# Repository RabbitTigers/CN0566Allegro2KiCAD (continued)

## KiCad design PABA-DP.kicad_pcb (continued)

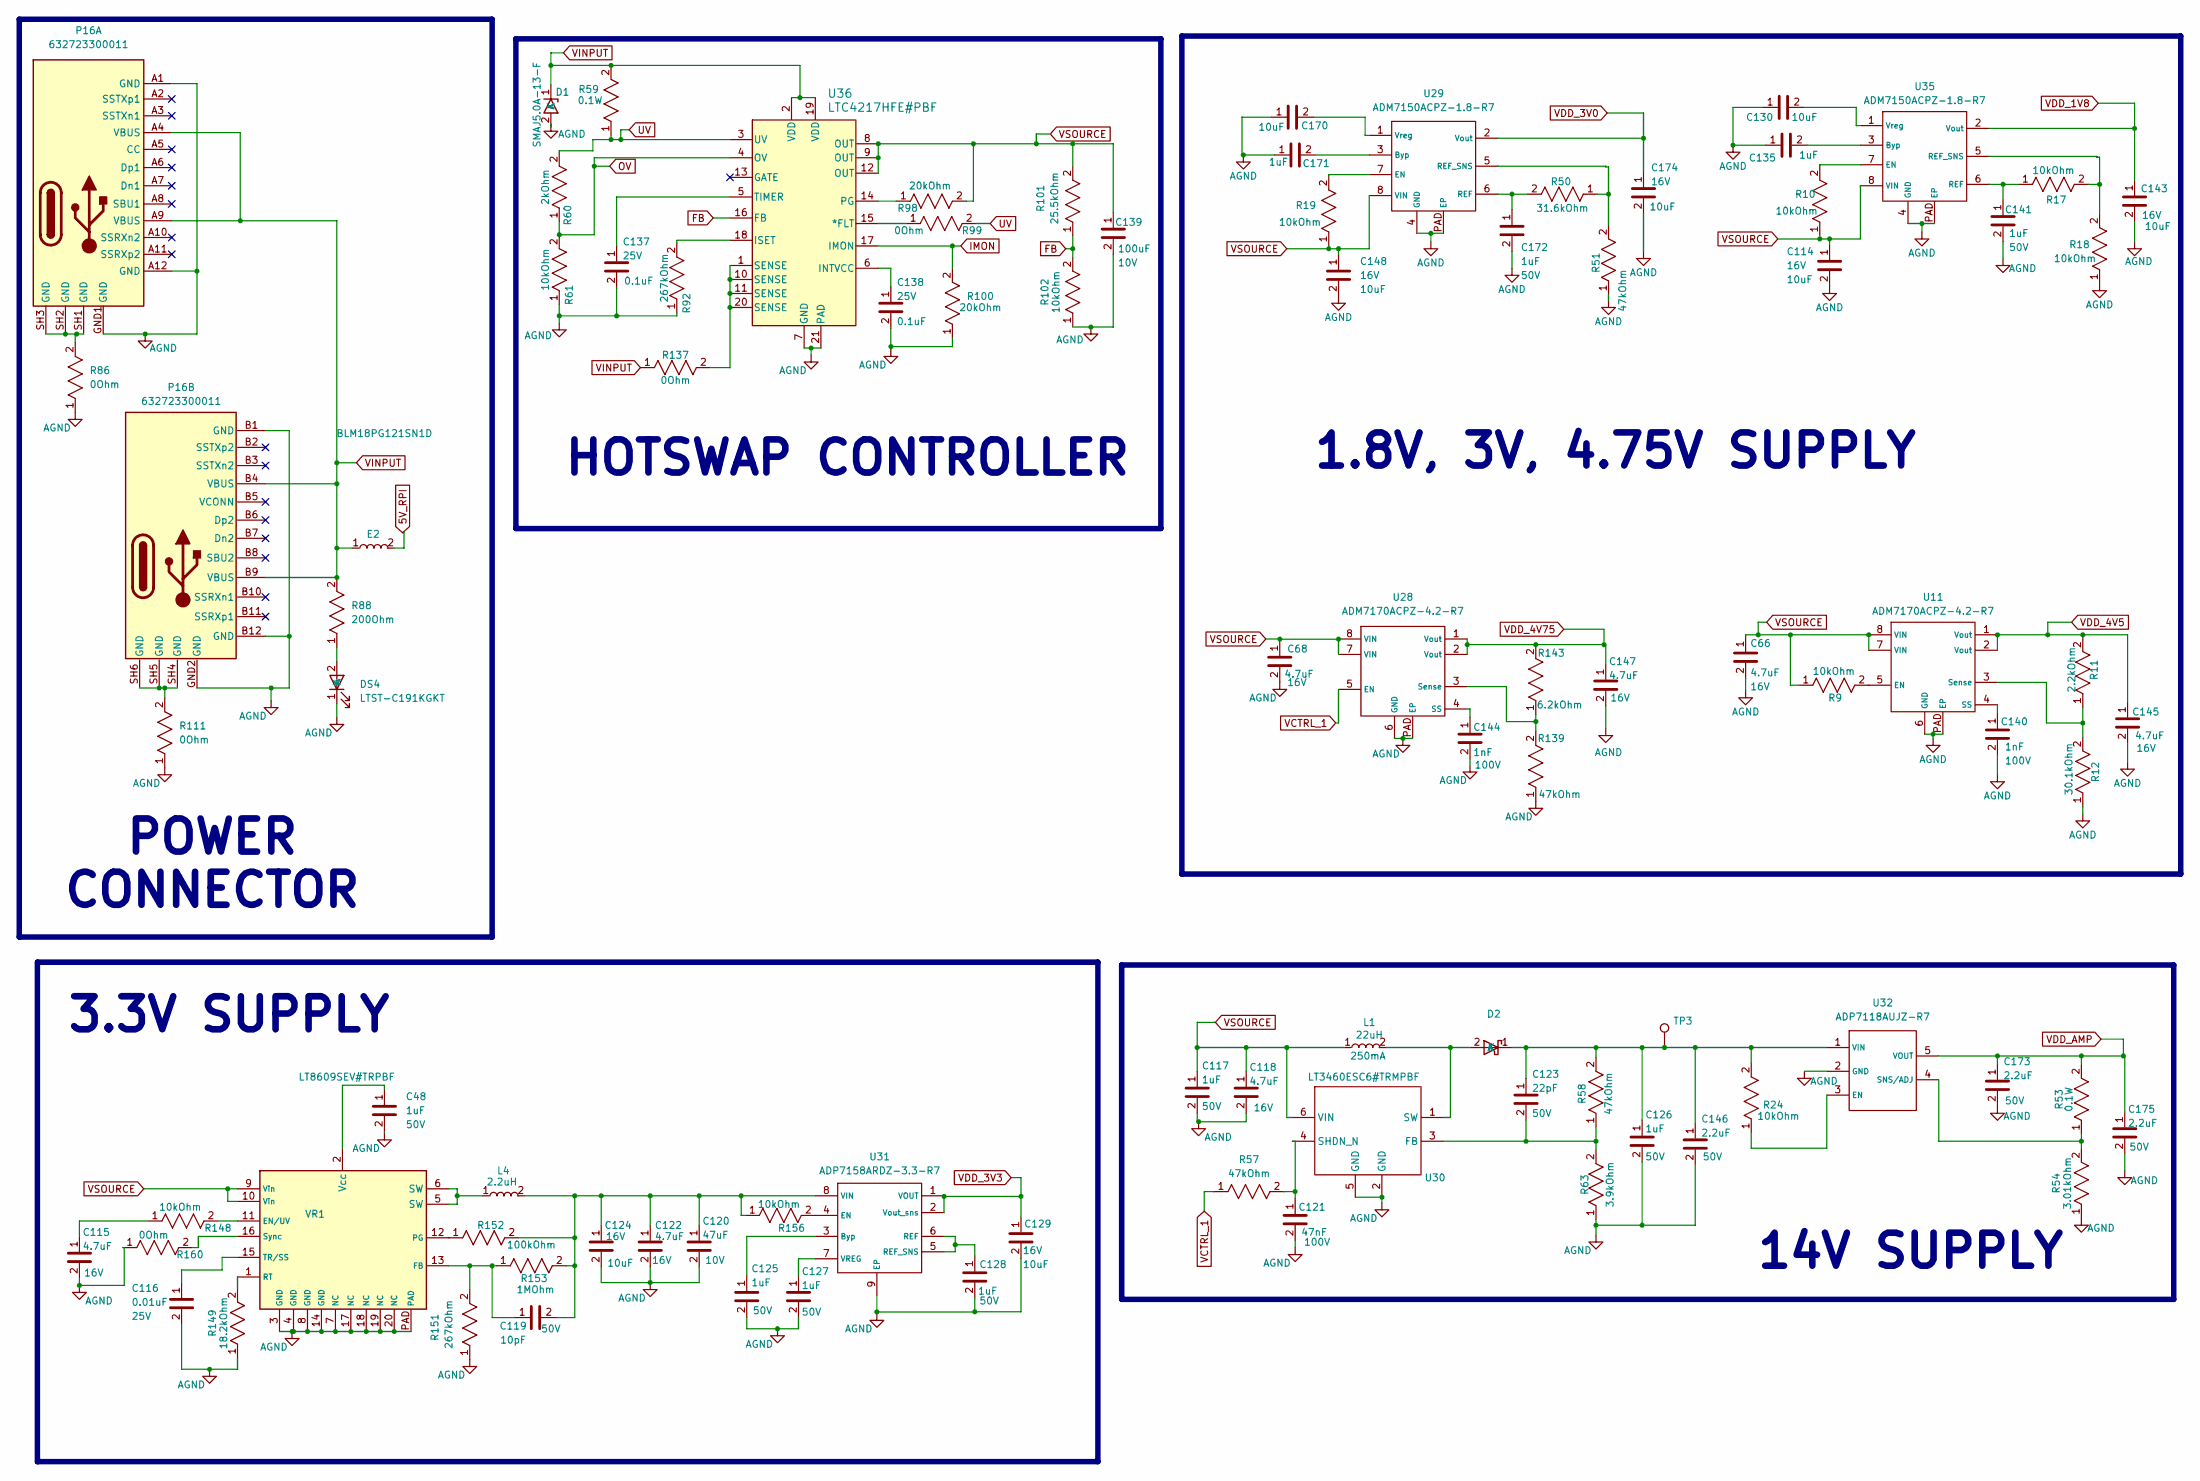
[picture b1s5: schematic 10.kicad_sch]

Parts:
C48, C117, C125, C126, C127, C128, C135, C141, C171, C172: CL10A105KB8NNNC; C_0603_1608Metric
C66, C68, C115, C118, C122, C145, C147: GRM188C81C475KE11D; C_0603_1608Metric
C114, C124, C129, C130, C143, C148, C170, C174: GRM188R61C106KAALD; C_0603_1608Metric
C116: CL10B103KA8NNNC; C_0603_1608Metric
C119: CL10C100JB8NNNC; C_0603_1608Metric
C120: LMK325B7476KM-PR; C_1210_3225Metric
C121: C0603C473K1RACAUTO; C_0603_1608Metric
C123: 06035C220JAT2A; C_0603_1608Metric
C137, C138: CL10B104KA8NNNC; C_0603_1608Metric
C139: CL32A107MPVNNNE; C_1210_3225Metric
C140, C144: 06031C102KAT2A; C_0603_1608Metric
C146, C173, C175: GRM188R61H225KE11J; C_0603_1608Metric
D1: SMAJ5.0A-13-F; D_SMA
D2: CMDSH2-3_TR_PBFREE; D_SOD-323
DS4: LTST-C191KGKT; LED_0603_1608Metric
E2: BLM18PG121SN1D; L_0603_1608Metric
L1: LQH32CN220K53L; LQH32CH100K53L
L4: XFL4020-222MEB; XFL4020-222ME
P16: 632723300011
R9, R10, R17, R18, R19, R24, R61, R102, R148, R156: ERJ-3EKF1002V; R_0603_1608Metric
R11: ERJ-3EKF2201V; R_0603_1608Metric
R12: ERJ-3EKF3012V; R_0603_1608Metric
R50, R53, R59: ERJ-3EKF3162V; R_0603_1608Metric
R51, R57, R58, R139: ERJ-3EKF4702V; R_0603_1608Metric
R54: ERJ-3EKF3011V; R_0603_1608Metric
R60: ERJ-3EKF2001V; R_0603_1608Metric
R63: ERJ-2RKF3901X; R_0402_1005Metric
R86, R99, R111, R137, R160: ERJ-3GEY0R00V; R_0603_1608Metric
R88: ERJ-3EKF2000V; R_0603_1608Metric
R92, R151: CRCW0603267KFKEA; R_0603_1608Metric
R98, R100: ERJ-3EKF2002V; R_0603_1608Metric
R101: ERJ-3EKF2552V; R_0603_1608Metric
R143: ERJ-2RKF6201X; R_0603_1608Metric
R149: ERJ-3EKF1822V; R_0603_1608Metric
R152: ERJ-3EKF1003V; R_0603_1608Metric
R153: ERJ-3EKF1004V; R_0603_1608Metric
TP3: TestPoint; Testpoint
U11, U28: ADM7170ACPZ-4.2-R7; ADM7170ACPZ-4.2-R7 lfcsp 3x3
U29, U35: ADM7150ACPZ-1.8-R7; ADM7170ACPZ-4.2-R7 lfcsp 3x3
U30: LT3460ESC6#TRMPBF; LT3460ESC6#TRMPBF sc-70-6 sc-88
U31: ADP7158ARDZ-3.3-R7; SOIC-8-1EP_3.9x4.9mm_P1.27mm_EP2.29x3mm
U32: ADP7118AUJZ-R7; TSOT-23-5
U36: LTC4217HFE#PBF; HTSSOP-20-1EP_4.4x6.5mm_P0.65mm_EP3.4x6.5mm_Mask2.4x3.7mm
VR1: LT8609SEV#TRPBF

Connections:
5V_RPI: E2.2; also elsewhere on the board
AGND: C48.2, C66.2, C68.2, C114.2, C115.2, C116.2, C117.2, C118.2, C120.2, C121.2, C122.2, C124.2, C125.2, C126.2, C127.2, C128.2, C129.2, C130.1, C135.1, C137.2, C138.2, C139.2, C140.2, C141.2, C143.2, C144.2, C145.2, C146.2, C147.2, C148.2, C170.1, C171.1, C172.2, C173.2, C174.2, C175.2, D1.2 (A), DS4.1 (K), P16.A1 (GND), P16.A12 (GND), P16.B1 (GND), P16.B12 (GND), P16.GND1 (GND), P16.GND2 (GND), R12.1, R18.1, R51.1, R54.1, R61.1, R63.1, R86.1, R92.1, R100.1, R102.1, R111.1, R139.1, R149.1, R151.1, R160.1, U11.6 (GND), U11.PAD (EP), U28.6 (GND), U28.PAD (EP), U29.4 (GND), U29.PAD (EP), U30.2 (GND), U30.5 (GND), U31.9 (EP), U32.2 (GND), U35.4 (GND), U35.PAD (EP), U36.7 (GND), U36.21 (PAD), VR1.3 (GND), VR1.4 (GND), VR1.7 (NC), VR1.8 (GND), VR1.14 (GND), VR1.17 (NC), VR1.18 (NC), VR1.19 (NC), VR1.20 (NC), VR1.PAD; also elsewhere on the board
FB: R101.1, R102.2, U36.16 (FB)
IMON: R100.2, U36.17 (IMON); also elsewhere on the board
unnamed: C115.1, R148.1
unnamed: D2.2 (A), L1.2, U30.1 (SW)
unnamed: C123.1, C126.1, C146.1, D2.1 (K), R24.2, R58.2, TP3.1, U32.1 (VIN)
unnamed: DS4.2 (A), R88.1
unnamed: L4.1, VR1.5 (SW), VR1.6 (SW)
unnamed: P16.SH1 (GND), P16.SH2 (GND), P16.SH3 (GND), R86.2
unnamed: P16.SH4 (GND), P16.SH5 (GND), P16.SH6 (GND), R111.2
unnamed: R137.2, U36.1 (SENSE), U36.10 (SENSE), U36.11 (SENSE), U36.20 (SENSE)
unnamed: R9.2, U11.5 (EN)
unnamed: C140.1, U11.4 (SS)
unnamed: R11.1, R12.2, U11.3 (Sense)
unnamed: C144.1, U28.4 (SS)
unnamed: R139.2, R143.1, U28.3 (Sense)
unnamed: C171.2, U29.3 (Byp)
unnamed: R19.2, U29.7 (EN)
unnamed: C172.1, R50.2, U29.6 (REF)
unnamed: R50.1, R51.2, U29.5 (REF_SNS)
unnamed: C170.2, U29.1 (Vreg)
unnamed: C123.2, R58.1, R63.2, U30.3 (FB)
unnamed: C121.1, R57.2, U30.4 (SHDN_N)
unnamed: C125.1, U31.3 (Byp)
unnamed: R156.2, U31.4 (EN)
unnamed: C128.1, U31.5 (REF_SNS), U31.6 (REF)
unnamed: C119.2, C120.1, C122.1, C124.1, L4.2, R152.2, R153.2, R156.1, U31.8 (VIN)
unnamed: C127.1, U31.7 (VREG)
unnamed: R24.1, U32.3 (EN)
unnamed: R53.1, R54.2, U32.4 (SNS/ADJ)
unnamed: C135.2, U35.3 (Byp)
unnamed: R10.2, U35.7 (EN)
unnamed: C141.1, R17.1, U35.6 (REF)
unnamed: R17.2, R18.2, U35.5 (REF_SNS)
unnamed: C130.2, U35.1 (Vreg)
unnamed: R99.1, U36.15 (*FLT)
unnamed: C138.1, U36.6 (INTVCC)
unnamed: R92.2, U36.18 (ISET)
unnamed: R98.1, U36.14 (PG)
unnamed: C137.1, U36.5 (TIMER)
unnamed: R148.2, VR1.11 (EN/UV)
unnamed: C119.1, R151.2, R153.1, VR1.13 (FB)
unnamed: R152.1, VR1.12 (PG)
unnamed: R149.2, VR1.1 (RT)
unnamed: R160.2, VR1.16 (Sync)
unnamed: C116.1, VR1.15 (TR/SS)
unnamed: C48.1, VR1.2 (Vcc)
OV: R60.1, R61.2, U36.4 (OV)
UV: R59.1, R60.2, R99.2, U36.3 (UV)
VCTRL_1: R57.1, U28.5 (EN); also elsewhere on the board
VDD_1V8: C143.1, U35.2 (Vout); also elsewhere on the board
VDD_3V0: C174.1, U29.2 (Vout); also elsewhere on the board
VDD_3V3: C129.1, U31.1 (VOUT), U31.2 (Vout_sns); also elsewhere on the board
VDD_4V5: C145.1, R11.2, U11.1 (Vout), U11.2 (Vout); also elsewhere on the board
VDD_4V75: C147.1, R143.2, U28.1 (Vout), U28.2 (Vout); also elsewhere on the board
VDD_AMP: C173.1, C175.1, R53.2, U32.5 (VOUT); also elsewhere on the board
VINPUT: D1.1 (K), E2.1, P16.A4 (VBUS), P16.A9 (VBUS), P16.B4 (VBUS), P16.B9 (VBUS), R59.2, R88.2, R137.1, U36.2 (VDD), U36.19 (VDD); also elsewhere on the board
VSOURCE: C66.1, C68.1, C114.1, C117.1, C118.1, C139.1, C148.1, L1.1, R9.1, R10.1, R19.1, R98.2, R101.2, U11.7 (VIN), U11.8 (VIN), U28.7 (VIN), U28.8 (VIN), U29.8 (VIN), U30.6 (VIN), U35.8 (VIN), U36.8 (OUT), U36.9 (OUT), U36.12 (OUT), VR1.9 (Vin), VR1.10 (Vin)

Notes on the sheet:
HOTSWAP CONTROLLER
3.3V SUPPLY
14V SUPPLY
1.8V, 3V, 4.75V SUPPLY
POWER CONNECTOR

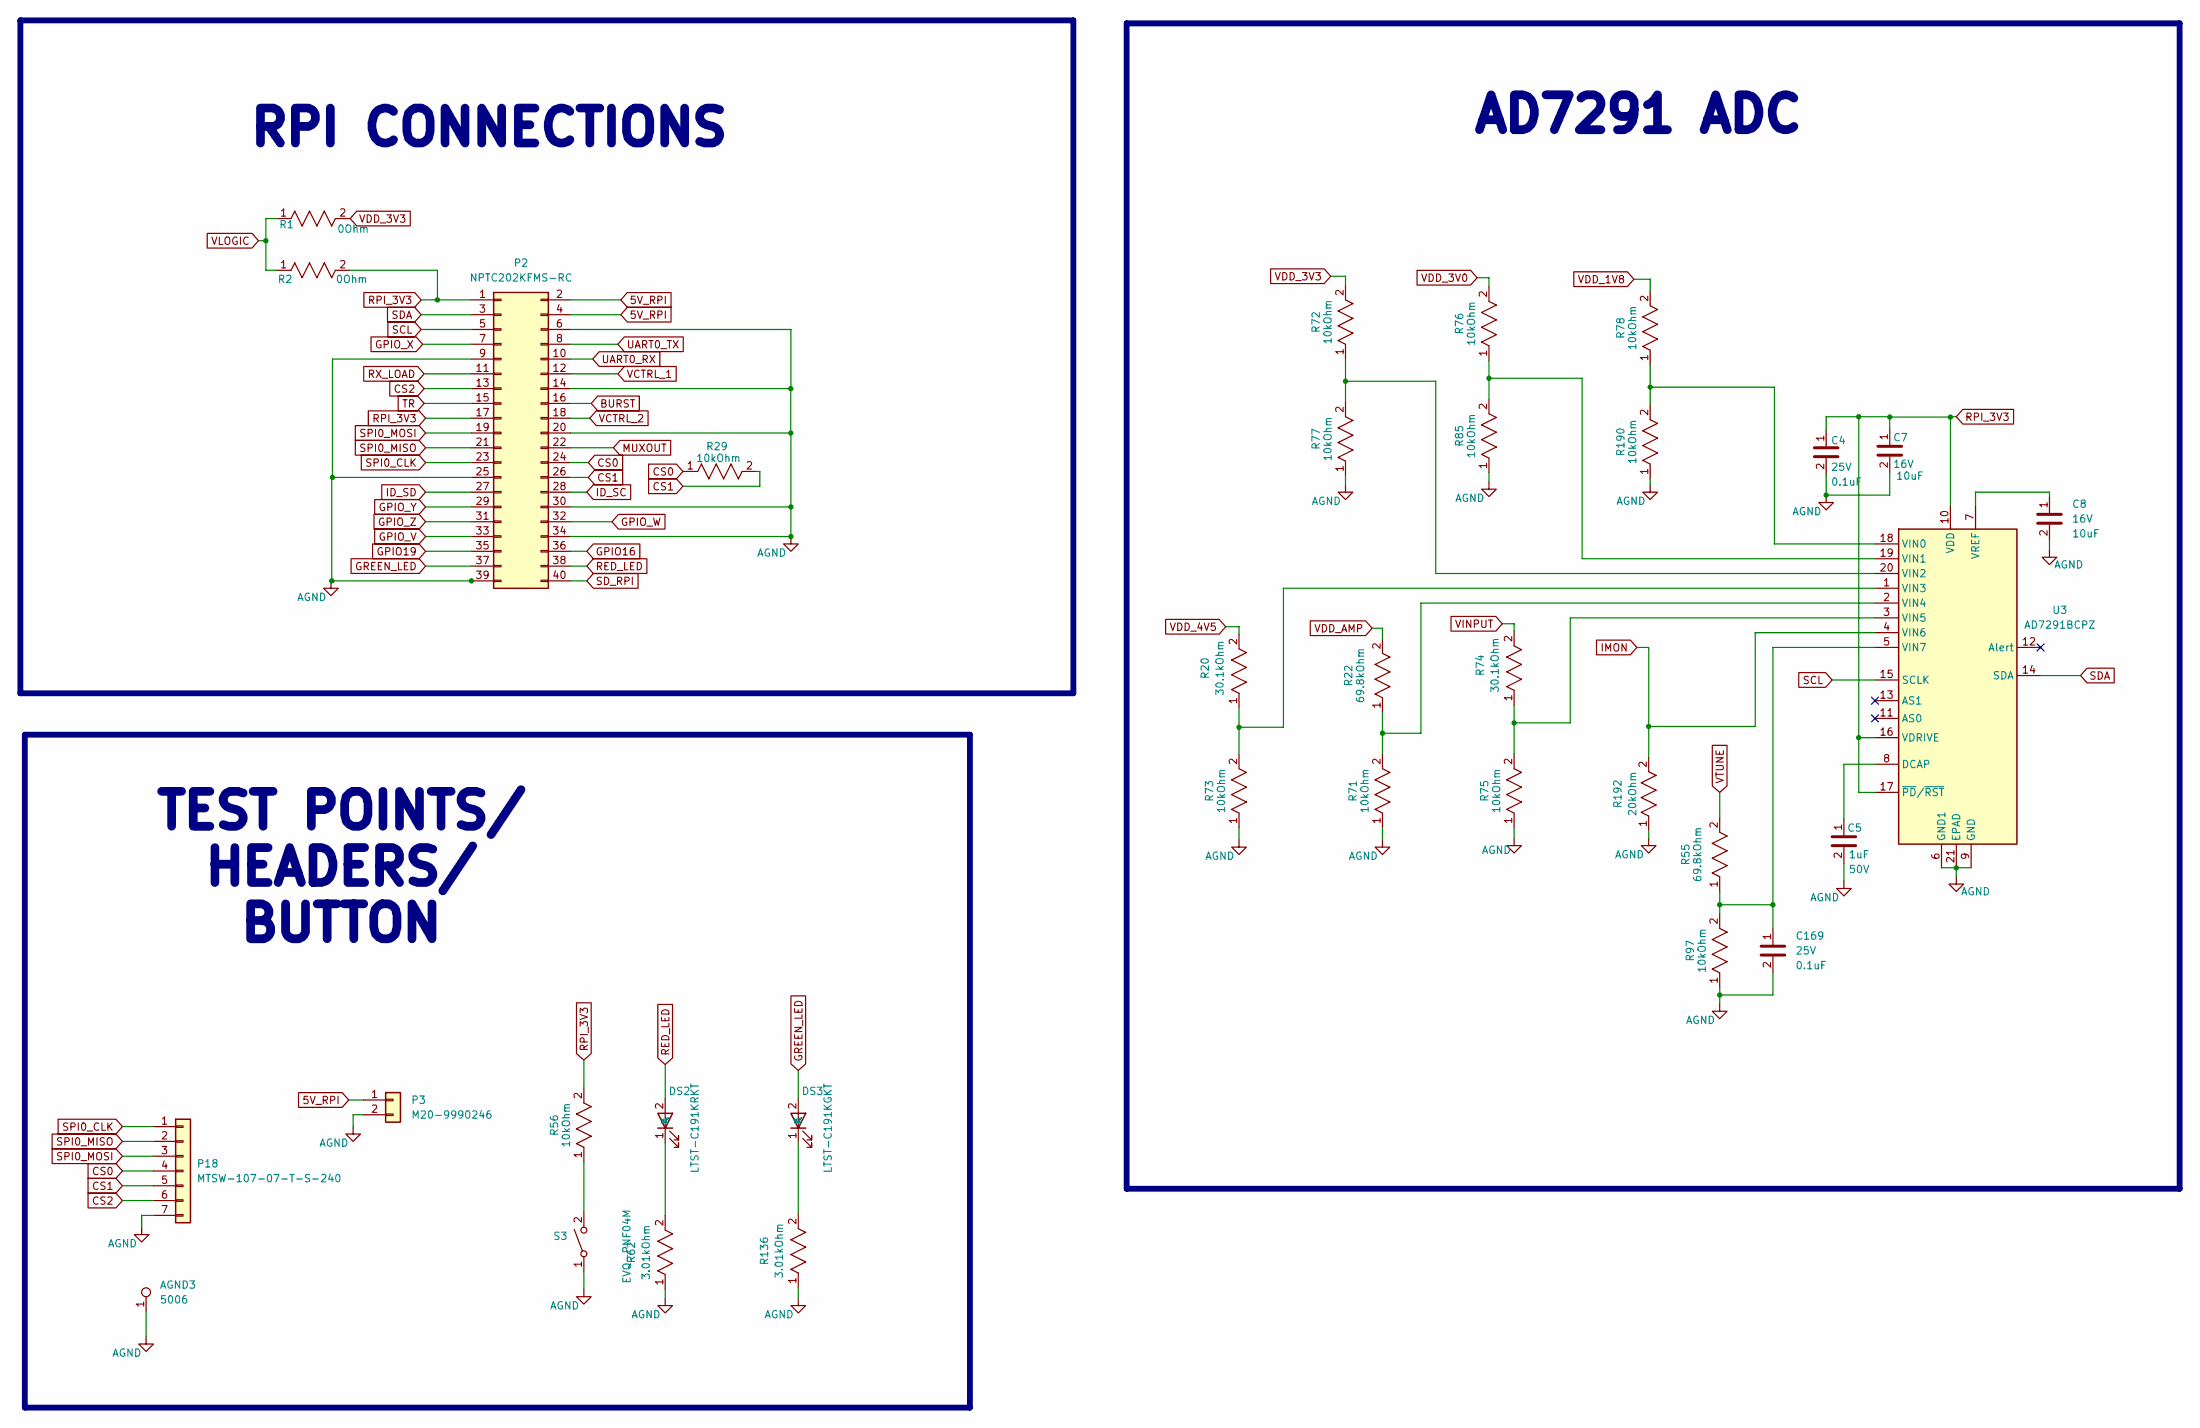
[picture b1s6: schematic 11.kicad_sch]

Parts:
AGND3: 5006; KEYSTONE_5009
C4, C169: CL10B104KA8NNNC; C_0603_1608Metric
C5: CL10A105KB8NNNC; C_0603_1608Metric
C7, C8: GRM188R61C106KAALD; C_0603_1608Metric
DS2: LTST-C191KRKT; LED_0603_1608Metric
DS3: LTST-C191KGKT; LED_0603_1608Metric
P2: NPTC202KFMS-RC; PinSocket_2x20_P2.54mm_Vertical_SMD
P3: M20-9990246; PinHeader_1x02_P2.54mm_Vertical
P18: MTSW-107-07-T-S-240; PinHeader_1x07_P2.54mm_Vertical
R1, R2: ERJ-3GEY0R00V; R_0603_1608Metric
R20, R74: ERJ-3EKF3012V; R_0603_1608Metric
R22, R55: ERJ-3EKF6982V; R_0603_1608Metric
R29, R56, R71, R72, R73, R75, R76, R77, R78, R85, R97, R190: ERJ-3EKF1002V; R_0603_1608Metric
R62, R136: ERJ-3EKF3011V; R_0603_1608Metric
R192: ERJ-3EKF2002V; R_0603_1608Metric
S3: EVQ-PNF04M
U3: AD7291BCPZ; LFCSP-20-1EP_4x4mm_P0.5mm_EP2.6x2.6mm

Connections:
5V_RPI: P2.2, P2.4, P3.1; also elsewhere on the board
AGND: AGND3.1, C4.2, C5.2, C7.2, C8.2, C169.2, P2.6, P2.9, P2.14, P2.20, P2.25, P2.30, P2.34, P2.39, P3.2, P18.7, R62.1, R71.1, R73.1, R75.1, R77.1, R85.1, R97.1, R136.1, R190.1, R192.1, S3.1, U3.6 (GND1), U3.9 (GND), U3.21 (EPAD); also elsewhere on the board
BURST: P2.16; also elsewhere on the board
CS0: P2.24, P18.4, R29.1; also elsewhere on the board
CS1: P2.26, P18.5, R29.2; also elsewhere on the board
CS2: P2.13, P18.6; also elsewhere on the board
GPIO16: P2.36
GPIO19: P2.35
GPIO_V: P2.33; also elsewhere on the board
GPIO_W: P2.32; also elsewhere on the board
GPIO_X: P2.7; also elsewhere on the board
GPIO_Y: P2.29; also elsewhere on the board
GPIO_Z: P2.31; also elsewhere on the board
GREEN_LED: DS3.2 (A), P2.37
ID_SC: P2.28; also elsewhere on the board
ID_SD: P2.27; also elsewhere on the board
IMON: R192.2, U3.4 (VIN6); also elsewhere on the board
MUXOUT: P2.22; also elsewhere on the board
unnamed: DS2.1 (K), R62.2
unnamed: DS3.1 (K), R136.2
unnamed: R56.1, S3.2
unnamed: C5.1, U3.8 (DCAP)
unnamed: R78.1, R190.2, U3.18 (VIN0)
unnamed: R76.1, R85.2, U3.19 (VIN1)
unnamed: R72.1, R77.2, U3.20 (VIN2)
unnamed: R20.1, R73.2, U3.1 (VIN3)
unnamed: R22.1, R71.2, U3.2 (VIN4)
unnamed: R74.1, R75.2, U3.3 (VIN5)
unnamed: C169.1, R55.1, R97.2, U3.5 (VIN7)
unnamed: C8.1, U3.7 (VREF)
RED_LED: DS2.2 (A), P2.38
RPI_3V3: C4.1, C7.1, P2.1, P2.17, R2.2, R56.2, U3.10 (VDD), U3.16 (VDRIVE), U3.17 (~PD/~RST); also elsewhere on the board
RX_LOAD: P2.11; also elsewhere on the board
SCL: P2.5, U3.15 (SCLK); also elsewhere on the board
SDA: P2.3, U3.14 (SDA); also elsewhere on the board
SD_RPI: P2.40
SPI0_CLK: P2.23, P18.1; also elsewhere on the board
SPI0_MISO: P2.21, P18.2; also elsewhere on the board
SPI0_MOSI: P2.19, P18.3; also elsewhere on the board
TR: P2.15; also elsewhere on the board
UART0_RX: P2.10
UART0_TX: P2.8
VCTRL_1: P2.12; also elsewhere on the board
VCTRL_2: P2.18; also elsewhere on the board
VDD_1V8: R78.2; also elsewhere on the board
VDD_3V0: R76.2; also elsewhere on the board
VDD_3V3: R1.2, R72.2; also elsewhere on the board
VDD_4V5: R20.2; also elsewhere on the board
VDD_AMP: R22.2; also elsewhere on the board
VINPUT: R74.2; also elsewhere on the board
VLOGIC: R1.1, R2.1; also elsewhere on the board
VTUNE: R55.2; also elsewhere on the board

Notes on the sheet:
TEST POINTS/ HEADERS/ BUTTON
AD7291 ADC
RPI CONNECTIONS

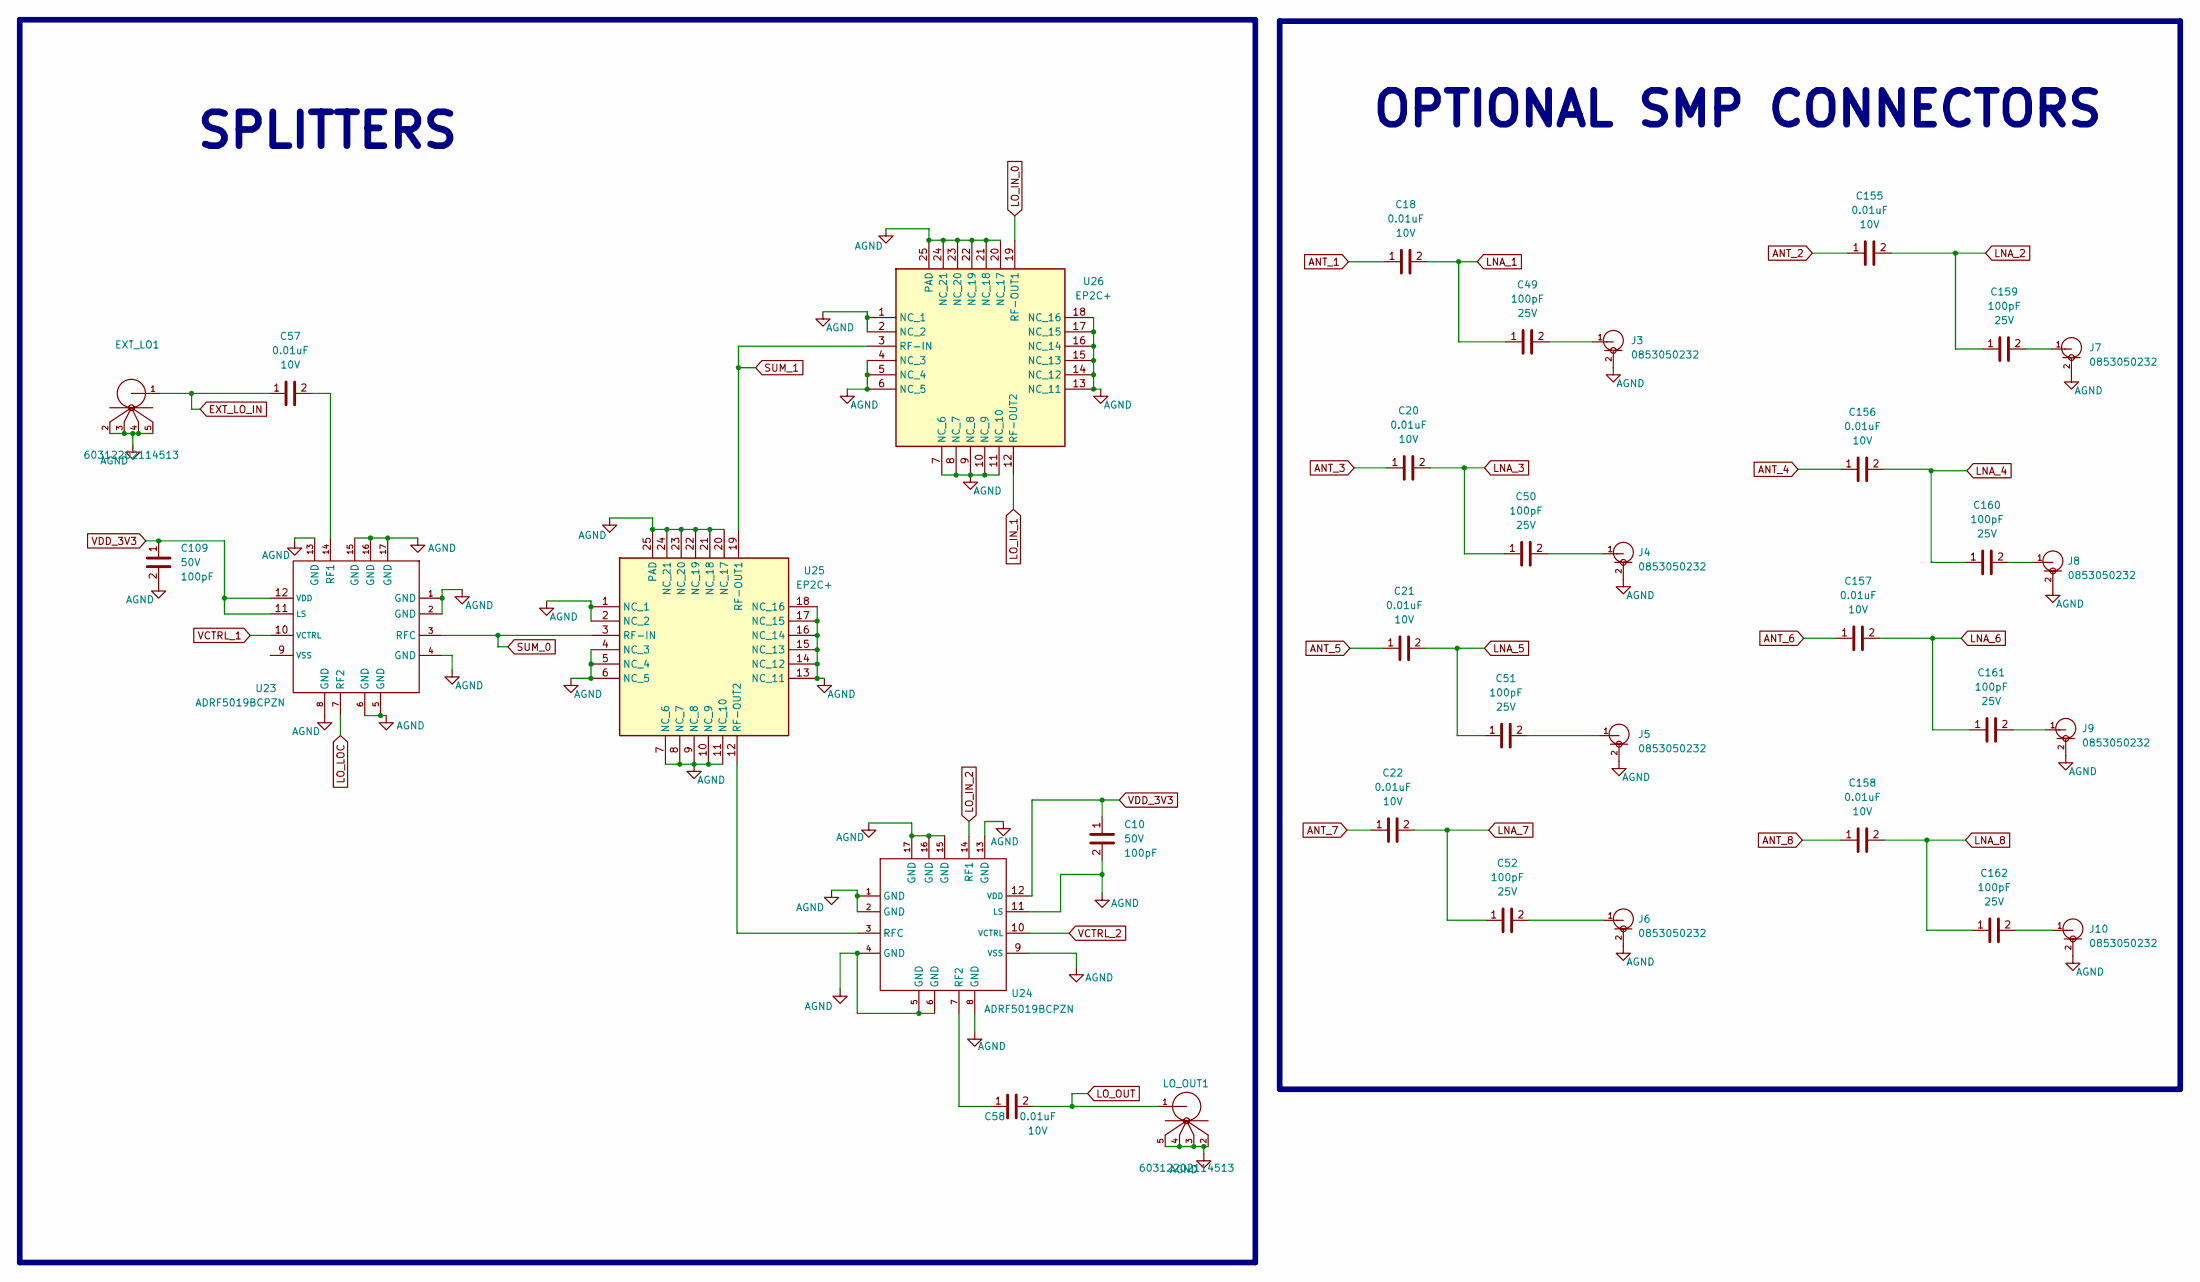
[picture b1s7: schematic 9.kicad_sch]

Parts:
C10, C109: CC0603KRX7R9BB101; C_0603_1608Metric
C18, C20, C21, C22, C57, C58, C155, C156, C157, C158: GRM033R71A103KA01D; C_0201_0603Metric
C49, C50, C51, C52, C159, C160, C161, C162: GRM033R71E101KA01D; C_0201_0603Metric
EXT_LO1: 60312202114513
J3, J4, J5, J6, J7, J8, J9, J10: 0853050232; MOLEX_85305-0232
LO_OUT1: 60312202114513
U23, U24: ADRF5019BCPZN; LFCSP-16-1EP_3x3mm_P0.5mm_EP1.7x1.7mm
U25, U26: EP2C+; QFN-24-1EP_4x4mm_P0.5mm_EP2.6x2.6mm

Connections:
AGND: C10.2, C109.2, EXT_LO1.2, EXT_LO1.3, EXT_LO1.4, EXT_LO1.5, J3.2, J4.2, J5.2, J6.2, J7.2, J8.2, J9.2, J10.2, LO_OUT1.2, LO_OUT1.3, LO_OUT1.4, LO_OUT1.5, U23.1 (GND), U23.2 (GND), U23.4 (GND), U23.5 (GND), U23.6 (GND), U23.8 (GND), U23.13 (GND), U23.15 (GND), U23.16 (GND), U23.17 (GND), U24.1 (GND), U24.2 (GND), U24.4 (GND), U24.5 (GND), U24.6 (GND), U24.8 (GND), U24.9 (VSS), U24.11 (LS), U24.13 (GND), U24.15 (GND), U24.16 (GND), U24.17 (GND), U25.1 (NC_1), U25.2 (NC_2), U25.4 (NC_3), U25.5 (NC_4), U25.6 (NC_5), U25.7 (NC_6), U25.8 (NC_7), U25.9 (NC_8), U25.10 (NC_9), U25.11 (NC_10), U25.13 (NC_11), U25.14 (NC_12), U25.15 (NC_13), U25.16 (NC_14), U25.17 (NC_15), U25.18 (NC_16), U25.20 (NC_17), U25.21 (NC_18), U25.22 (NC_19), U25.23 (NC_20), U25.24 (NC_21), U25.25 (PAD), U26.1 (NC_1), U26.2 (NC_2), U26.4 (NC_3), U26.5 (NC_4), U26.6 (NC_5), U26.7 (NC_6), U26.8 (NC_7), U26.9 (NC_8), U26.10 (NC_9), U26.11 (NC_10), U26.13 (NC_11), U26.14 (NC_12), U26.15 (NC_13), U26.16 (NC_14), U26.17 (NC_15), U26.18 (NC_16), U26.20 (NC_17), U26.21 (NC_18), U26.22 (NC_19), U26.23 (NC_20), U26.24 (NC_21), U26.25 (PAD); also elsewhere on the board
ANT_1: C18.1; also elsewhere on the board
ANT_2: C155.1; also elsewhere on the board
ANT_3: C20.1; also elsewhere on the board
ANT_4: C156.1; also elsewhere on the board
ANT_5: C21.1; also elsewhere on the board
ANT_6: C157.1; also elsewhere on the board
ANT_7: C22.1; also elsewhere on the board
ANT_8: C158.1; also elsewhere on the board
EXT_LO_IN: C57.1, EXT_LO1.1
LNA_1: C18.2, C49.1; also elsewhere on the board
LNA_2: C155.2, C159.1; also elsewhere on the board
LNA_3: C20.2, C50.1; also elsewhere on the board
LNA_4: C156.2, C160.1; also elsewhere on the board
LNA_5: C21.2, C51.1; also elsewhere on the board
LNA_6: C157.2, C161.1; also elsewhere on the board
LNA_7: C22.2, C52.1; also elsewhere on the board
LNA_8: C158.2, C162.1; also elsewhere on the board
LO_IN_0: U26.19 (RF-OUT1); also elsewhere on the board
LO_IN_1: U26.12 (RF-OUT2); also elsewhere on the board
LO_IN_2: U24.14 (RF1); also elsewhere on the board
LO_LOC: U23.7 (RF2); also elsewhere on the board
LO_OUT: C58.2, LO_OUT1.1
unnamed: C49.2, J3.1
unnamed: C50.2, J4.1
unnamed: C51.2, J5.1
unnamed: C52.2, J6.1
unnamed: C159.2, J7.1
unnamed: C160.2, J8.1
unnamed: C161.2, J9.1
unnamed: C162.2, J10.1
unnamed: C57.2, U23.14 (RF1)
unnamed: C58.1, U24.7 (RF2)
unnamed: U24.3 (RFC), U25.12 (RF-OUT2)
SUM_0: U23.3 (RFC), U25.3 (RF-IN)
SUM_1: U25.19 (RF-OUT1), U26.3 (RF-IN)
VCTRL_1: U23.10 (VCTRL); also elsewhere on the board
VCTRL_2: U24.10 (VCTRL); also elsewhere on the board
VDD_3V3: C10.1, C109.1, U23.11 (LS), U23.12 (VDD), U24.12 (VDD); also elsewhere on the board

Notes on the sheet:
OPTIONAL SMP CONNECTORS
SPLITTERS

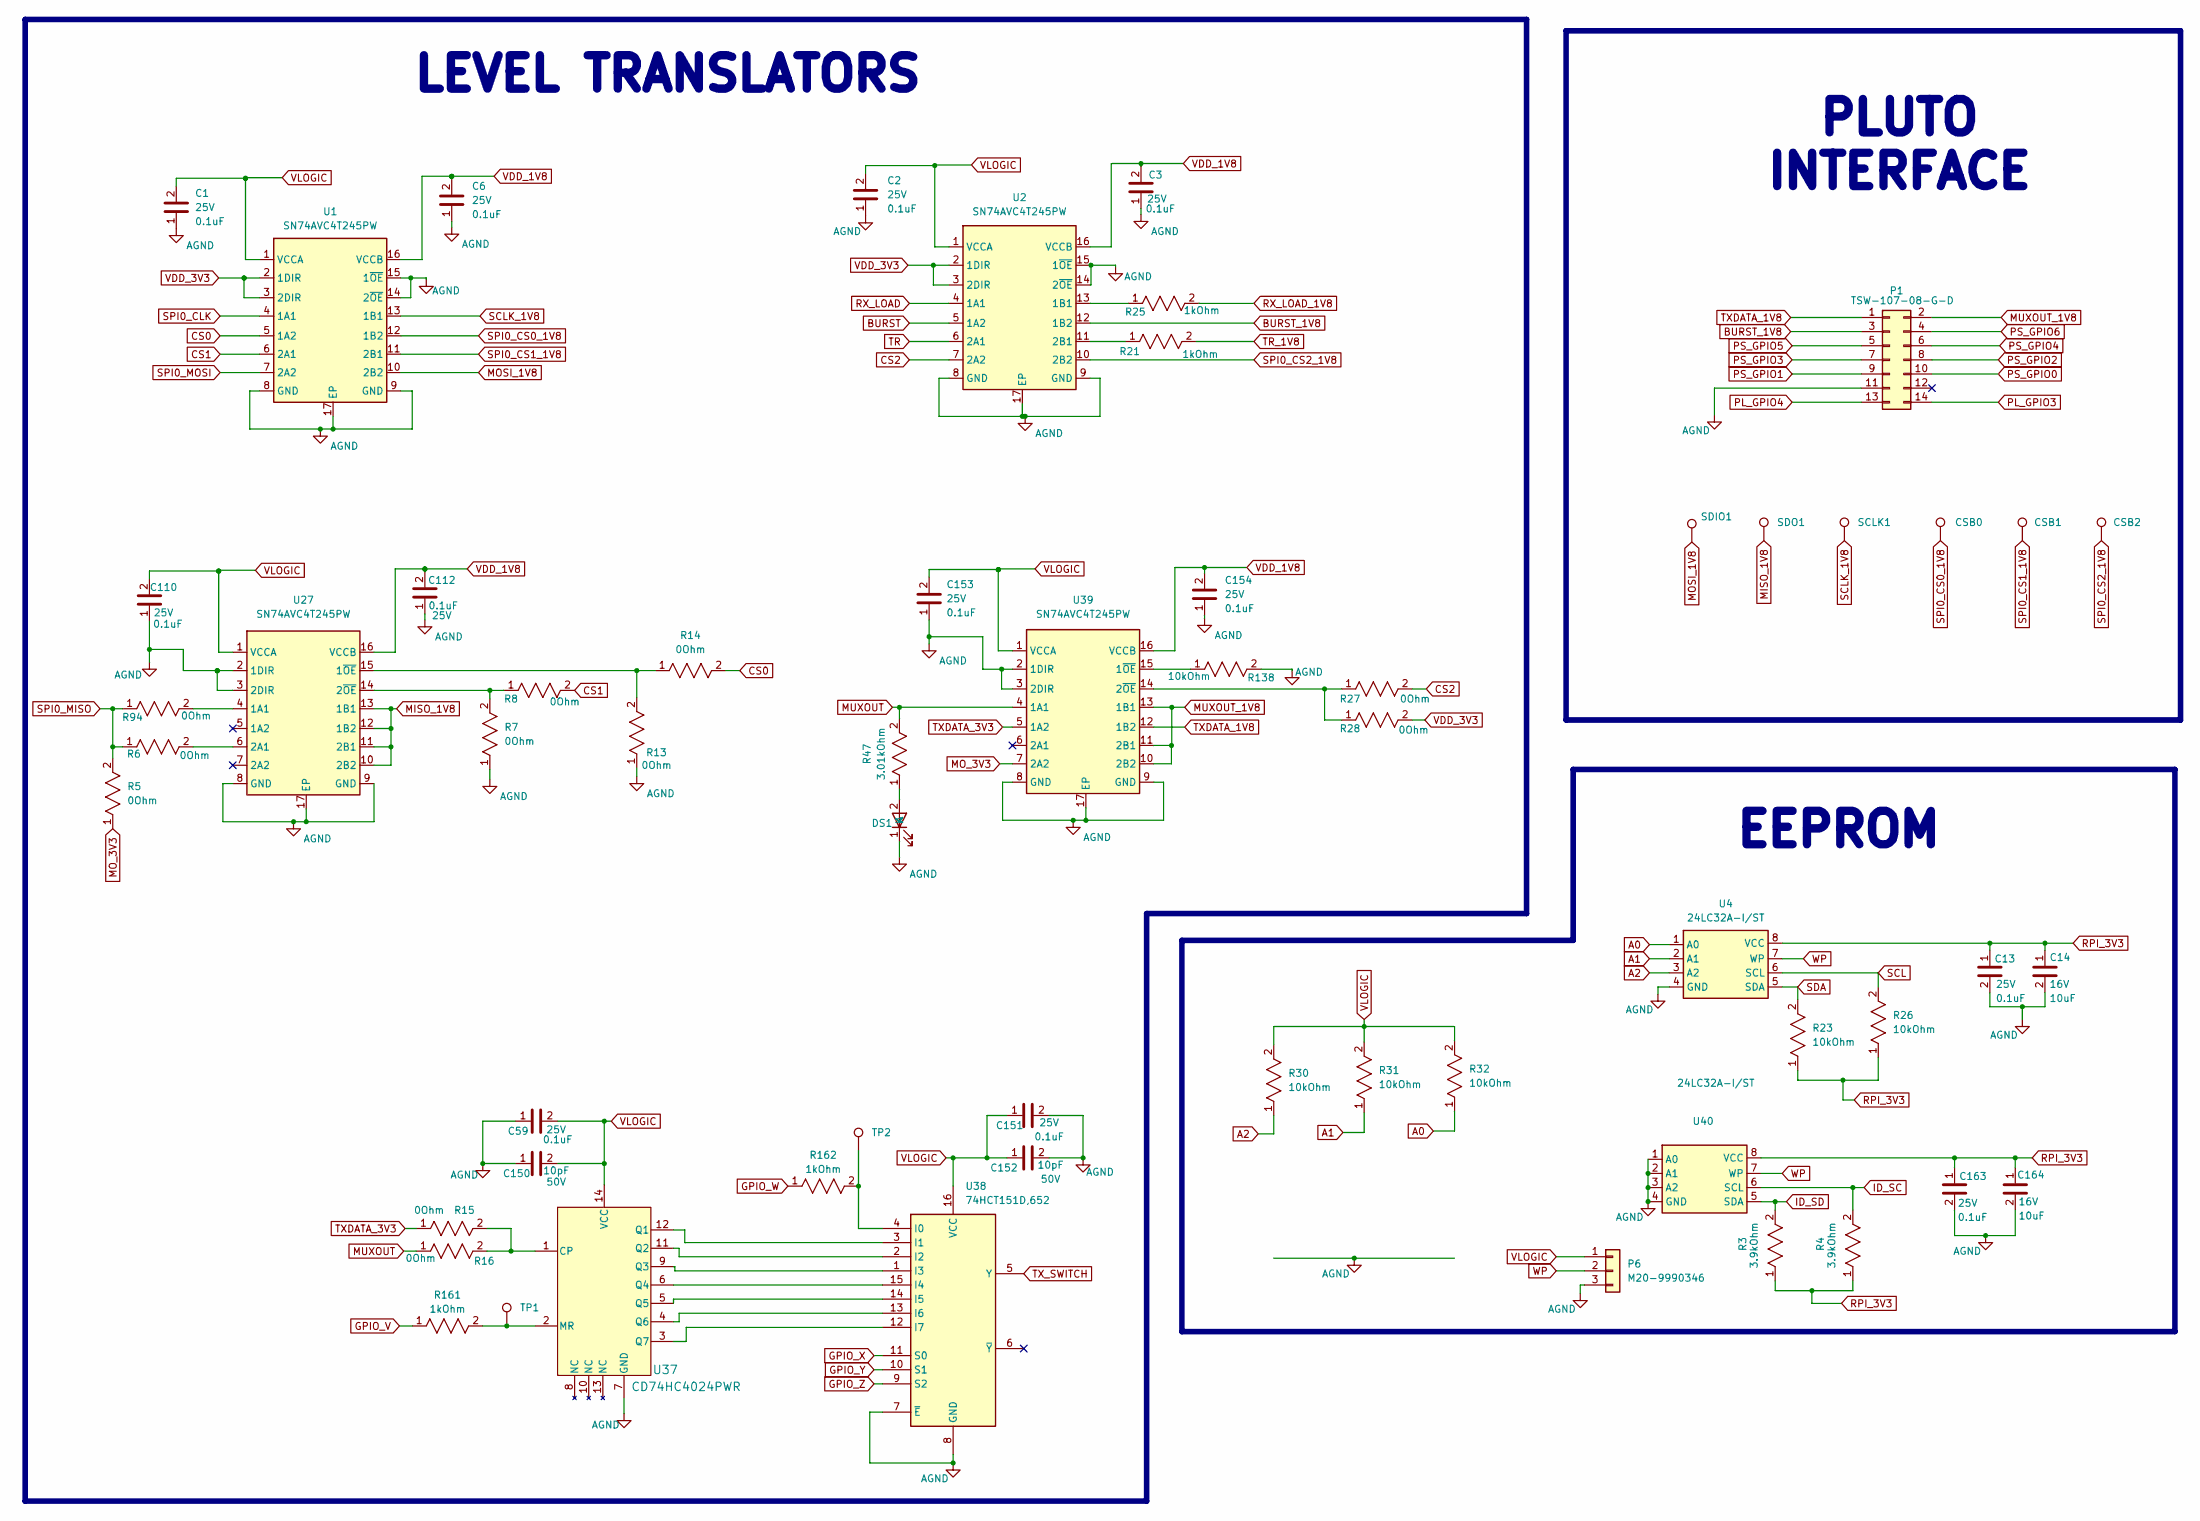
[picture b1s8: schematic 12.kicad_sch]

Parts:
C1, C2, C3, C6, C13, C59, C110, C112, C151, C153, C154, C163: CL10B104KA8NNNC; C_0603_1608Metric
C14, C164: GRM188R61C106KAALD; C_0603_1608Metric
C150, C152: CL10C100JB8NNNC; C_0603_1608Metric
CSB0, CSB1, CSB2: TestPoint; Testpoint
DS1: 150060YS75000; LED_0603_1608Metric
P1: TSW-107-08-G-D; PinHeader_2x07_P2.54mm_Vertical
P6: M20-9990346; PinHeader_1x03_P2.54mm_Vertical
R3, R4: ERJ-2RKF3901X; R_0402_1005Metric
R5, R6, R7, R8, R13, R14, R15, R16, R27, R28, R94: ERJ-3GEY0R00V; R_0603_1608Metric
R21, R25, R161, R162: ERJ-3EKF1001V; R_0603_1608Metric
R23, R26, R30, R31, R32, R138: ERJ-3EKF1002V; R_0603_1608Metric
R47: ERJ-3EKF3011V; R_0603_1608Metric
SCLK1: TestPoint; Testpoint
SDIO1: TestPoint; Testpoint
SDO1: TestPoint; Testpoint
TP1, TP2: TestPoint; Testpoint
U1, U2, U27, U39: SN74AVC4T245PW; TSSOP-16-1EP_4.4x5mm_P0.65mm_EP3x3mm
U4, U40: 24LC32A-I/ST; TSSOP-8_4.4x3mm_P0.65mm
U37: CD74HC4024PWR; TSSOP-14_4.4x5mm_P0.65mm
U38: 74HCT151D,652; SOIC-16_3.9x9.9mm_P1.27mm

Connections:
A0: R32.1, U4.1 (A0)
A1: R31.1, U4.2 (A1)
A2: R30.1, U4.3 (A2)
AGND: C1.1, C2.1, C3.1, C6.1, C13.2, C14.2, C59.1, C110.1, C112.1, C150.1, C151.2, C152.2, C153.1, C154.1, C163.2, C164.2, DS1.1 (K), P1.11, P6.3, R7.1, R13.1, R138.2, U1.8 (GND), U1.9 (GND), U1.14 (2~OE), U1.15 (1~OE), U1.17 (EP), U2.8 (GND), U2.9 (GND), U2.14 (2~OE), U2.15 (1~OE), U2.17 (EP), U4.4 (GND), U27.2 (1DIR), U27.3 (2DIR), U27.8 (GND), U27.9 (GND), U27.17 (EP), U37.7 (GND), U38.7 (~E), U38.8 (GND), U39.2 (1DIR), U39.3 (2DIR), U39.8 (GND), U39.9 (GND), U39.17 (EP), U40.1 (A0), U40.2 (A1), U40.3 (A2), U40.4 (GND); also elsewhere on the board
BURST: U2.5 (1A2); also elsewhere on the board
BURST_1V8: P1.3, U2.12 (1B2)
CS0: R14.2, U1.5 (1A2); also elsewhere on the board
CS1: R8.2, U1.6 (2A1); also elsewhere on the board
CS2: R27.2, U2.7 (2A2); also elsewhere on the board
GPIO_V: R161.1; also elsewhere on the board
GPIO_W: R162.1; also elsewhere on the board
GPIO_X: U38.11 (S0); also elsewhere on the board
GPIO_Y: U38.10 (S1); also elsewhere on the board
GPIO_Z: U38.9 (S2); also elsewhere on the board
ID_SC: R4.2, U40.6 (SCL); also elsewhere on the board
ID_SD: R3.2, U40.5 (SDA); also elsewhere on the board
MISO_1V8: SDO1.1, U27.10 (2B2), U27.11 (2B1), U27.12 (1B2), U27.13 (1B1); also elsewhere on the board
MOSI_1V8: SDIO1.1, U1.10 (2B2); also elsewhere on the board
MO_3V3: R5.1, U39.7 (2A2)
MUXOUT: R16.1, R47.2, U39.4 (1A1); also elsewhere on the board
MUXOUT_1V8: P1.2, U39.10 (2B2), U39.11 (2B1), U39.13 (1B1); also elsewhere on the board
unnamed: DS1.2 (A), R47.1
unnamed: R25.1, U2.13 (1B1)
unnamed: R21.1, U2.11 (2B1)
unnamed: R94.2, U27.4 (1A1)
unnamed: R13.2, R14.1, U27.15 (1~OE)
unnamed: R6.2, U27.6 (2A1)
unnamed: R7.2, R8.1, U27.14 (2~OE)
unnamed: R15.2, R16.2, U37.1 (CP)
unnamed: R161.2, TP1.1, U37.2 (MR)
unnamed: U37.12 (Q1), U38.3 (I1)
unnamed: U37.11 (Q2), U38.2 (I2)
unnamed: U37.9 (Q3), U38.1 (I3)
unnamed: U37.6 (Q4), U38.15 (I4)
unnamed: U37.5 (Q5), U38.14 (I5)
unnamed: U37.4 (Q6), U38.13 (I6)
unnamed: U37.3 (Q7), U38.12 (I7)
unnamed: R162.2, TP2.1, U38.4 (I0)
unnamed: R138.1, U39.15 (1~OE)
unnamed: R27.1, R28.1, U39.14 (2~OE)
PL_GPIO3: P1.14
PL_GPIO4: P1.13
PS_GPIO0: P1.10
PS_GPIO1: P1.9
PS_GPIO2: P1.8
PS_GPIO3: P1.7
PS_GPIO4: P1.6
PS_GPIO5: P1.5
PS_GPIO6: P1.4
RPI_3V3: C13.1, C14.1, C163.1, C164.1, R3.1, R4.1, R23.1, R26.1, U4.8 (VCC), U40.8 (VCC); also elsewhere on the board
RX_LOAD: U2.4 (1A1); also elsewhere on the board
RX_LOAD_1V8: R25.2; also elsewhere on the board
SCL: R26.2, U4.6 (SCL); also elsewhere on the board
SCLK_1V8: SCLK1.1, U1.13 (1B1); also elsewhere on the board
SDA: R23.2, U4.5 (SDA); also elsewhere on the board
SPI0_CLK: U1.4 (1A1); also elsewhere on the board
SPI0_CS0_1V8: CSB0.1, U1.12 (1B2); also elsewhere on the board
SPI0_CS1_1V8: CSB1.1, U1.11 (2B1); also elsewhere on the board
SPI0_CS2_1V8: CSB2.1, U2.10 (2B2); also elsewhere on the board
SPI0_MISO: R5.2, R6.1, R94.1; also elsewhere on the board
SPI0_MOSI: U1.7 (2A2); also elsewhere on the board
TR: U2.6 (2A1); also elsewhere on the board
TR_1V8: R21.2; also elsewhere on the board
TXDATA_1V8: P1.1, U39.12 (1B2); also elsewhere on the board
TXDATA_3V3: R15.1, U39.5 (1A2)
TX_SWITCH: U38.5 (Y); also elsewhere on the board
VDD_1V8: C3.2, C6.2, C112.2, C154.2, U1.16 (VCCB), U2.16 (VCCB), U27.16 (VCCB), U39.16 (VCCB); also elsewhere on the board
VDD_3V3: R28.2, U1.2 (1DIR), U1.3 (2DIR), U2.2 (1DIR), U2.3 (2DIR); also elsewhere on the board
VLOGIC: C1.2, C2.2, C59.2, C110.2, C150.2, C151.1, C152.1, C153.2, P6.1, R30.2, R31.2, R32.2, U1.1 (VCCA), U2.1 (VCCA), U27.1 (VCCA), U37.14 (VCC), U38.16 (VCC), U39.1 (VCCA); also elsewhere on the board
WP: P6.2, U4.7 (WP), U40.7 (WP)

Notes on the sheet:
PLUTO INTERFACE
LEVEL TRANSLATORS
EEPROM

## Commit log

2025-06-02 final update
2025-06-02 Final
